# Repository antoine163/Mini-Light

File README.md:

# Mini Light
This is a small brightness control for desktop / workbench  / ... 
This is composed several parts:
- The control box: To enclose the power supply/electronic and sliders control.
- Light support for shelf: To attach the lights under shelf.
- Light support for prusa: To attach the lights  on prusa 3D printer.
- Wire Ties: To attach some cables.

## Control box
 
For more detail see: [Meca/control_box/README.md](Meca/control_box/README.md) 

## Light support for shelf
 
For more detail see: [Meca/light_support_for_shelf/README.md](Meca/light_support_for_shelf/README.md) 

## Light support for prusa
 
For more detail see: [Meca/light_support_for_shelf/README.md](Meca/light_support_for_prusa/README.md) 

# 3D Models
Some 3D models are not included in this project. You will need to download them from the manufacturers website if you need them.

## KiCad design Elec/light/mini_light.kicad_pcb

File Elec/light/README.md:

# Mini-Light Board
This board is a mini_light board.

Consumption max: 1.8W 

# Schematic

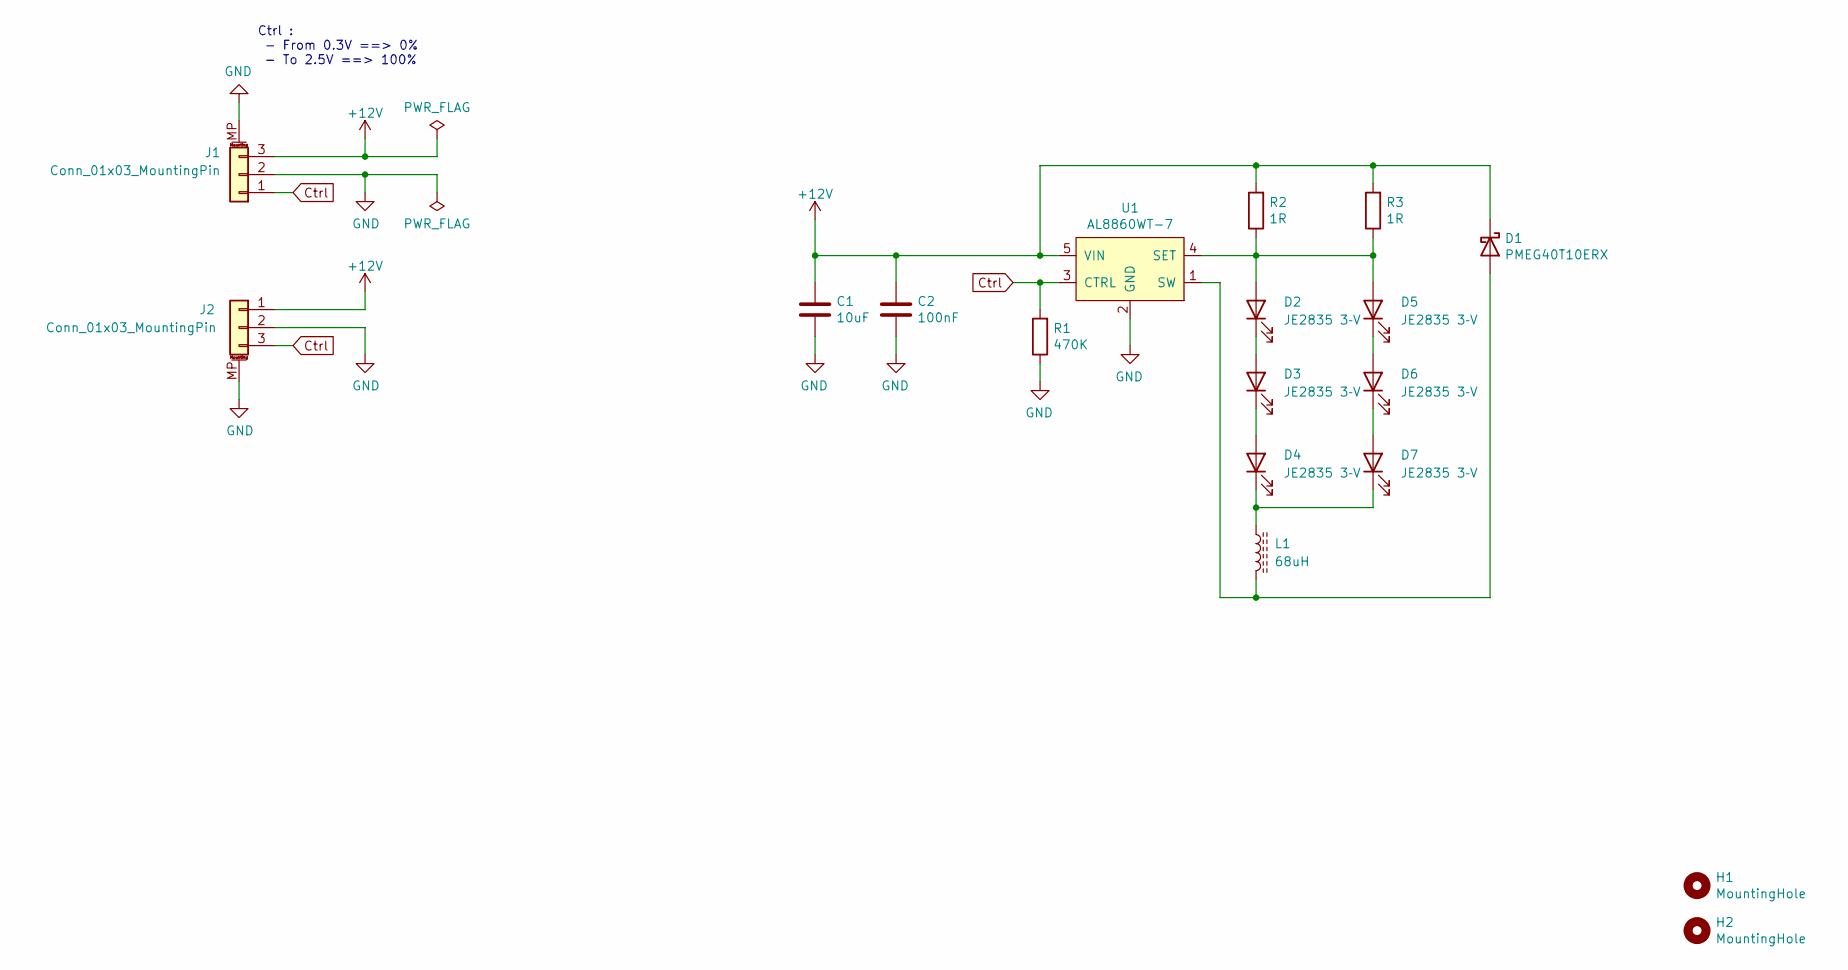
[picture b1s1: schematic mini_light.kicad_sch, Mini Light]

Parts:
C1: 10uF; C_0805_2012Metric_Pad1.18x1.45mm_HandSolder
C2: 100nF; C_0402_1005Metric_Pad0.74x0.62mm_HandSolder
D1: PMEG40T10ERX; Nexperia_CFP3_SOD-123W
D2, D3, D4, D5, D6, D7: JE2835 3‑V; LED_Cree-JE
H1, H2: MountingHole; MountingHole_3.2mm_M3
J1, J2: Conn_01x03_MountingPin; JST_PH_S3B-PH-SM4-TB_1x03-1MP_P2.00mm_Horizontal
L1: 68uH; L_Bourns-SRN5040
R1: 470K; R_0402_1005Metric_Pad0.72x0.64mm_HandSolder
R2, R3: 1R; R_0805_2012Metric_Pad1.20x1.40mm_HandSolder
U1: AL8860WT-7; TSOT-23-5

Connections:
+12V: C1.1, C2.1, D1.1 (K), J1.3, J2.1, R2.2, R3.2, U1.5 (VIN)
Ctrl: J1.1, J2.3, R1.2, U1.3 (CTRL)
GND: C1.2, C2.2, J1.2, J1.MP (MountPin), J2.2, J2.MP (MountPin), R1.1, U1.2 (GND)
unnamed: D1.2 (A), L1.2, U1.1 (SW)
unnamed: D2.1 (K), D3.2 (A)
unnamed: D2.2 (A), D5.2 (A), R2.1, R3.1, U1.4 (SET)
unnamed: D3.1 (K), D4.2 (A)
unnamed: D4.1 (K), D7.1 (K), L1.1
unnamed: D5.1 (K), D6.2 (A)
unnamed: D6.1 (K), D7.2 (A)

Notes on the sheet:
Ctrl : - From 0.3V ==> 0% - To 2.5V ==> 100%

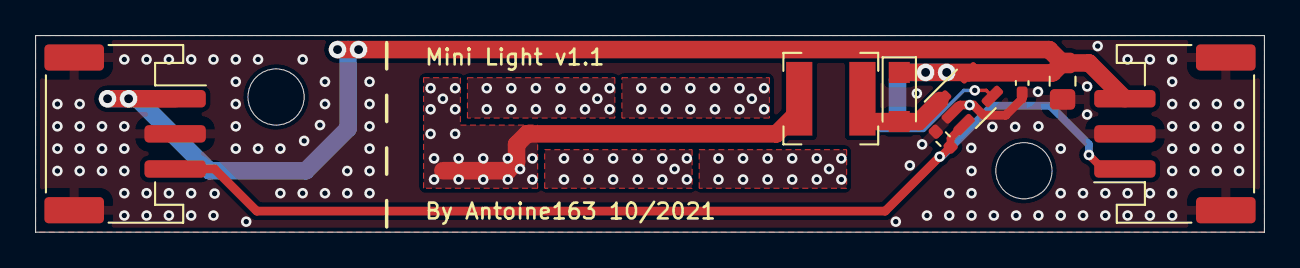
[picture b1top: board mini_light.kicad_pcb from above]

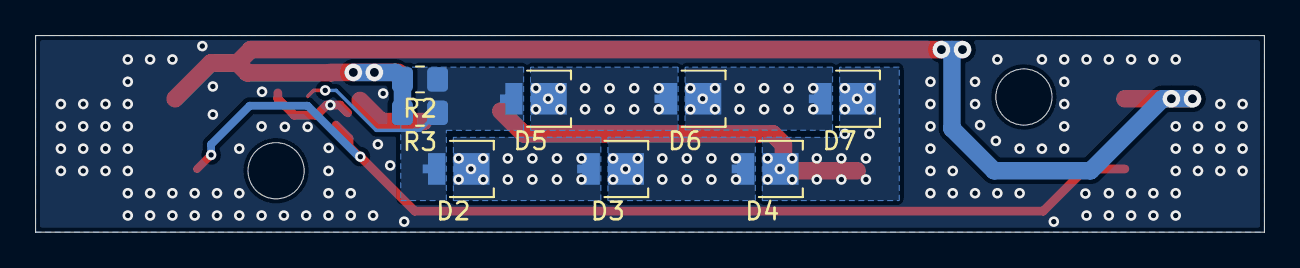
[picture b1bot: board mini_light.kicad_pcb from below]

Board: 2 copper layers, 70.0 x 11.2 mm, 18 parts (8 on the bottom side), 10 nets.

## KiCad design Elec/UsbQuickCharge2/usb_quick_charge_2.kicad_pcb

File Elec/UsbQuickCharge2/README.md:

# Usb Quick Charge 2.0

Circuit To enables 12V power on a USB Quick Charge 2.0 interface.
And brightness adjustment for Mini-Light.

# Schematic

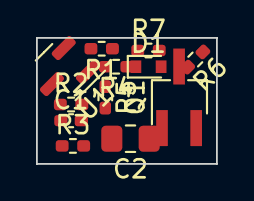
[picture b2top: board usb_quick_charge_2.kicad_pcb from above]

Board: 2 copper layers, 10.0 x 7.0 mm, 12 parts (0 on the bottom side), 6 nets, no tracks yet.

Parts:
C1: 100nF; C_0402_1005Metric_Pad0.74x0.62mm_HandSolder
C2: 10uF; C_0805_2012Metric_Pad1.18x1.45mm_HandSolder
D1: RB531SM-30FH; D_SOD-523
Q1: NX7002AKA; TSOT-23_HandSoldering
R1: 2K4; R_0402_1005Metric_Pad0.72x0.64mm_HandSolder
R2: 11K; R_0402_1005Metric_Pad0.72x0.64mm_HandSolder
R3: 130R; R_0402_1005Metric_Pad0.72x0.64mm_HandSolder
R4: 10K; R_0402_1005Metric_Pad0.72x0.64mm_HandSolder
R5, R6: 1K; R_0402_1005Metric_Pad0.72x0.64mm_HandSolder
R7: 470K; R_0402_1005Metric_Pad0.72x0.64mm_HandSolder
U1: TL431DBZ; SOT-23

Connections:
GND: C1.2, C2.2, R2.2, R3.2, R5.2, U1.3 (A)
unnamed: C2.1, D1.2 (A), Q1.1 (G), R7.2
unnamed: Q1.2 (S), R4.2, R5.1
unnamed: Q1.3 (D), R6.2
unnamed: R1.2, U1.1 (K), U1.2 (REF)
VCC: D1.1 (K), R1.1, R4.1, R7.1

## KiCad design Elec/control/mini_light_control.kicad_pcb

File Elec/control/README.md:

# Mini-Light-Control Board
This board can be power and control 4 different cluster of mini_light board.

# Schematic

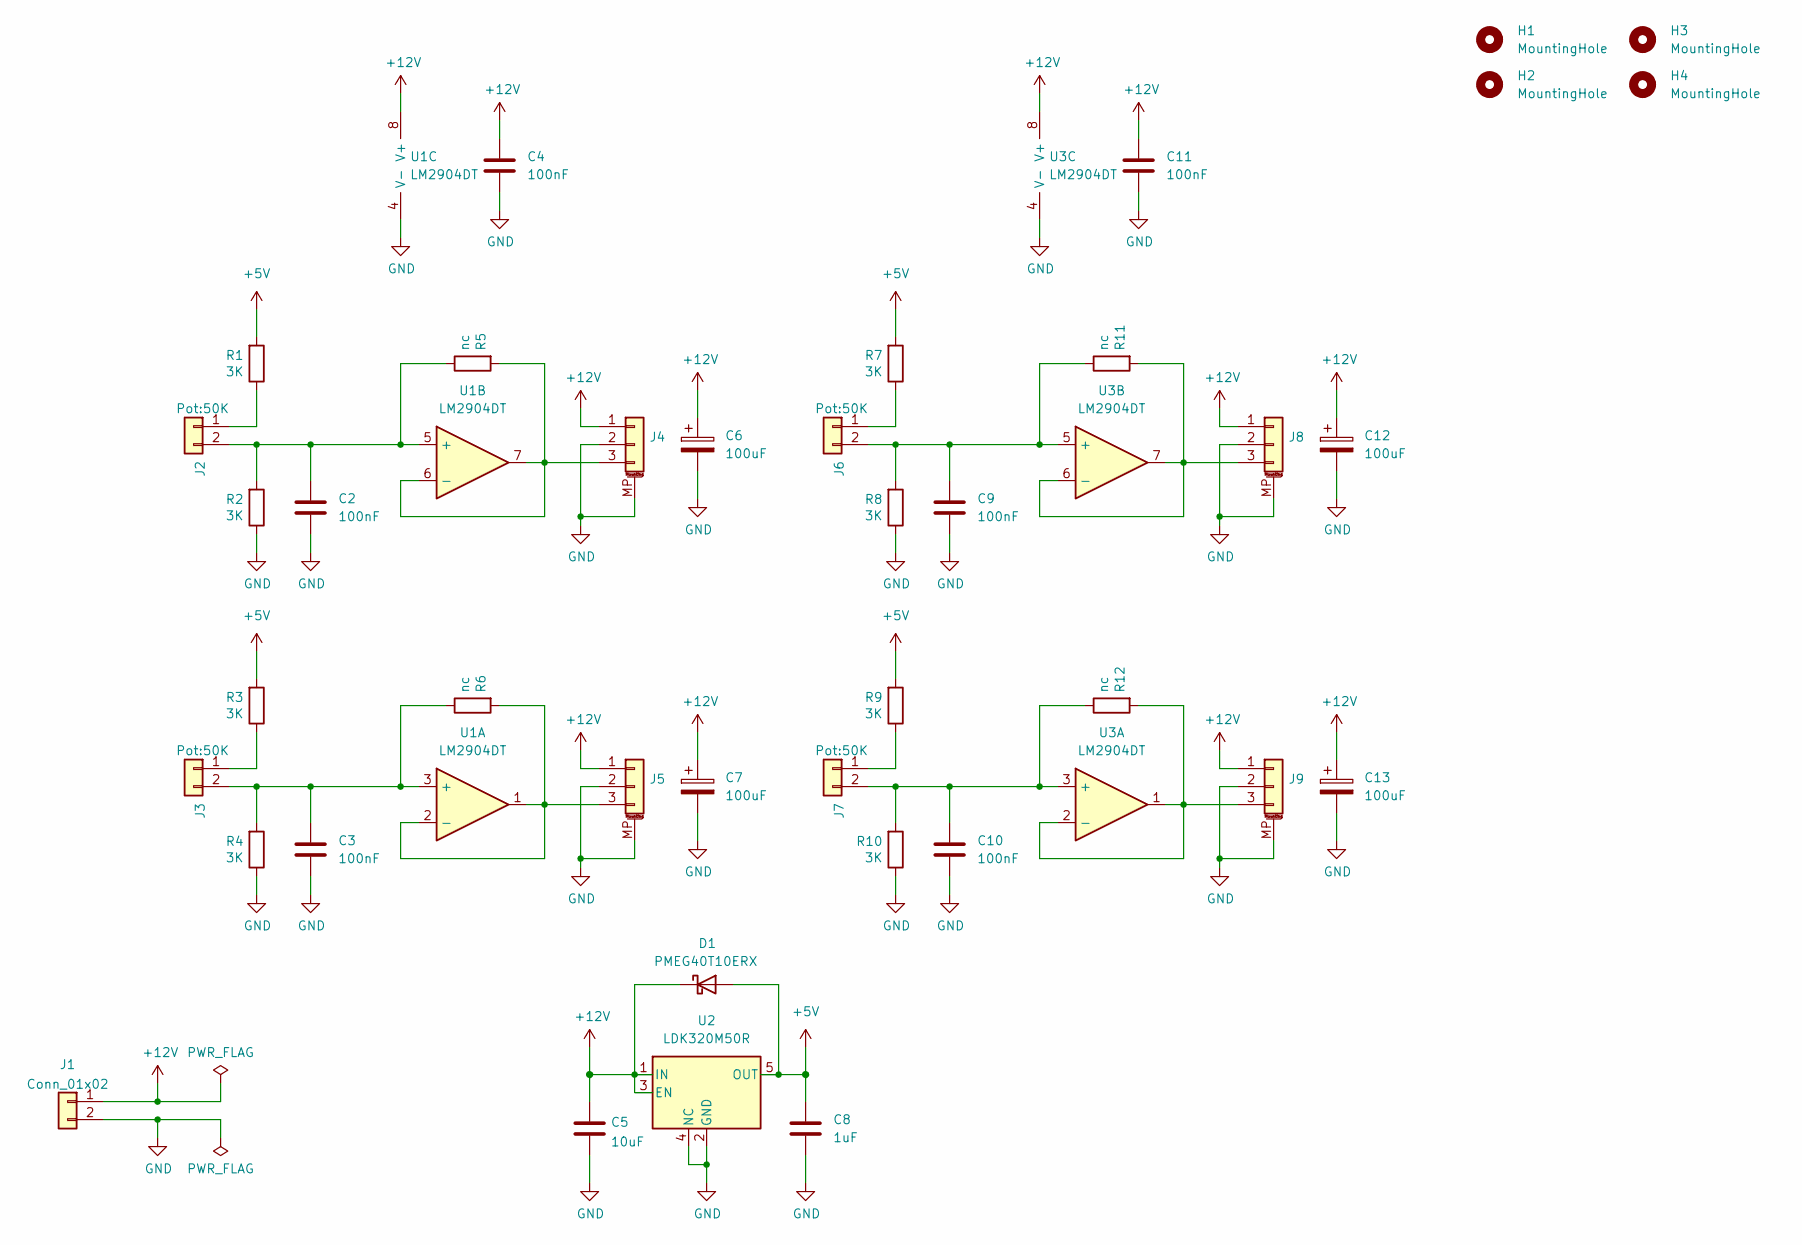
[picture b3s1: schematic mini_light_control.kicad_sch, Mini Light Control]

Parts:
C2, C3, C4, C9, C10, C11: 100nF; C_0402_1005Metric_Pad0.74x0.62mm_HandSolder
C5: 10uF; C_0805_2012Metric_Pad1.18x1.45mm_HandSolder
C6, C7, C12, C13: 100uF; CP_Elec_6.3x7.7
C8: 1uF; C_0603_1608Metric_Pad1.08x0.95mm_HandSolder
D1: PMEG40T10ERX; Nexperia_CFP3_SOD-123W
H1, H2, H3, H4: MountingHole; MountingHole_3.2mm_M3
J1, J2, J3, J6, J7: Conn_01x02; JST_PH_B2B-PH-K_1x02_P2.00mm_Vertical
J4, J5, J8, J9: Conn_01x03; JST_PH_S3B-PH-SM4-TB_1x03-1MP_P2.00mm_Horizontal
R1, R2, R3, R4, R7, R8, R9, R10: 3K; R_0402_1005Metric_Pad0.72x0.64mm_HandSolder
R5, R6, R11, R12: nc; R_0402_1005Metric_Pad0.72x0.64mm_HandSolder
U1, U3: LM2904DT; SOIC-8_3.9x4.9mm_P1.27mm
U2: LDK320M50R; SOT-23-5

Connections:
+5V: C8.1, D1.2 (A), R1.2, R3.2, R7.2, R9.2, U2.5 (OUT)
+12V: C4.1, C5.1, C6.1, C7.1, C11.1, C12.1, C13.1, D1.1 (K), J1.1, J4.1, J5.1, J8.1, J9.1, U1.8 (V+), U2.1 (IN), U2.3 (EN), U3.8 (V+)
GND: C2.2, C3.2, C4.2, C5.2, C6.2, C7.2, C8.2, C9.2, C10.2, C11.2, C12.2, C13.2, J1.2, J4.2, J4.MP (MountPin), J5.2, J5.MP (MountPin), J8.2, J8.MP (MountPin), J9.2, J9.MP (MountPin), R2.1, R4.1, R8.1, R10.1, U1.4 (V-), U2.2 (GND), U2.4 (NC), U3.4 (V-)
unnamed: C2.1, J2.2, R2.2, R5.1, U1.5 (+)
unnamed: C3.1, J3.2, R4.2, R6.1, U1.3 (+)
unnamed: C9.1, J6.2, R8.2, R11.1, U3.5 (+)
unnamed: C10.1, J7.2, R10.2, R12.1, U3.3 (+)
unnamed: J4.3, R5.2, U1.6 (-), U1.7
unnamed: J5.3, R6.2, U1.1, U1.2 (-)
unnamed: J8.3, R11.2, U3.6 (-), U3.7
unnamed: J9.3, R12.2, U3.1, U3.2 (-)
unnamed: J2.1, R1.1
unnamed: J3.1, R3.1
unnamed: J6.1, R7.1
unnamed: J7.1, R9.1

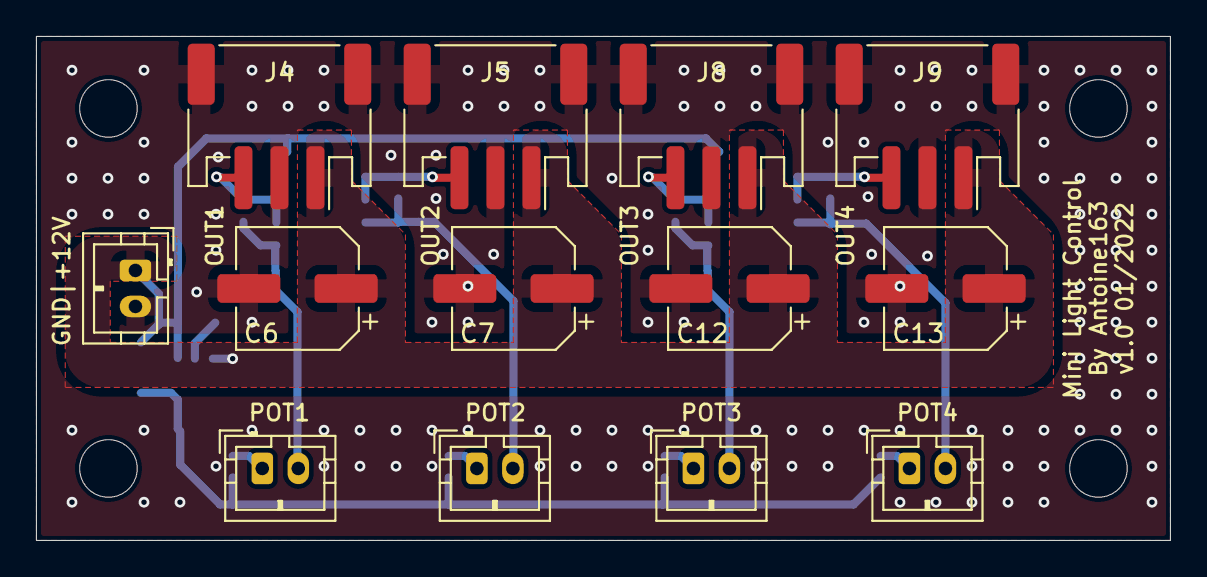
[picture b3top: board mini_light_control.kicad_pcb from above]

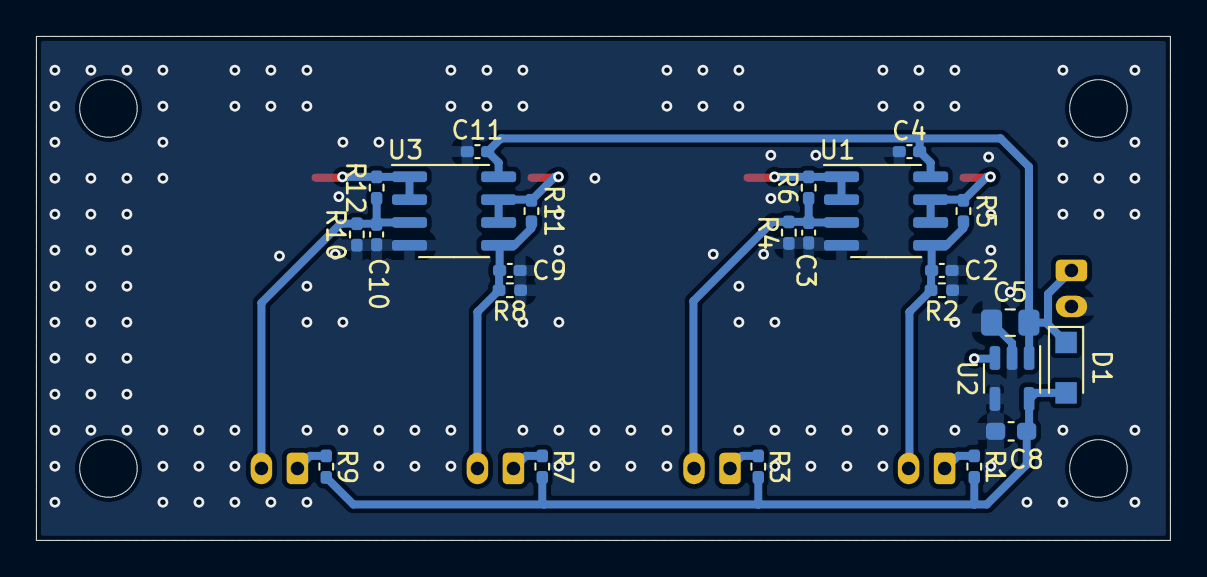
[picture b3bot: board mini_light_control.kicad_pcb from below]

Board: 2 copper layers, 63.0 x 28.0 mm, 41 parts (24 on the bottom side), 15 nets.

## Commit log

2021-10-05 Add kicad boards
2021-10-08 Update lib and pcb
2021-10-10 Add protection diode for LDO and change power connector.
2021-10-10 Change simbol connector to 'MountingPin' version
2022-01-04 Change JST connector polarity + regenerate gerber file
2022-03-13 add Meca folder and some readme
2022-05-21 control_box-AsPotsCap to v2
2022-05-21 Add file of control_box-AsPotsCap_v2
2022-07-01 Add light_support_for_prusa + pdf elec schematic
2022-10-22 add light_support_for_beam to fix a light on beam
2022-10-22 fix name in readme file
2023-01-14 Add UsbQuickCharge2
2024-03-17 update 3d step file
